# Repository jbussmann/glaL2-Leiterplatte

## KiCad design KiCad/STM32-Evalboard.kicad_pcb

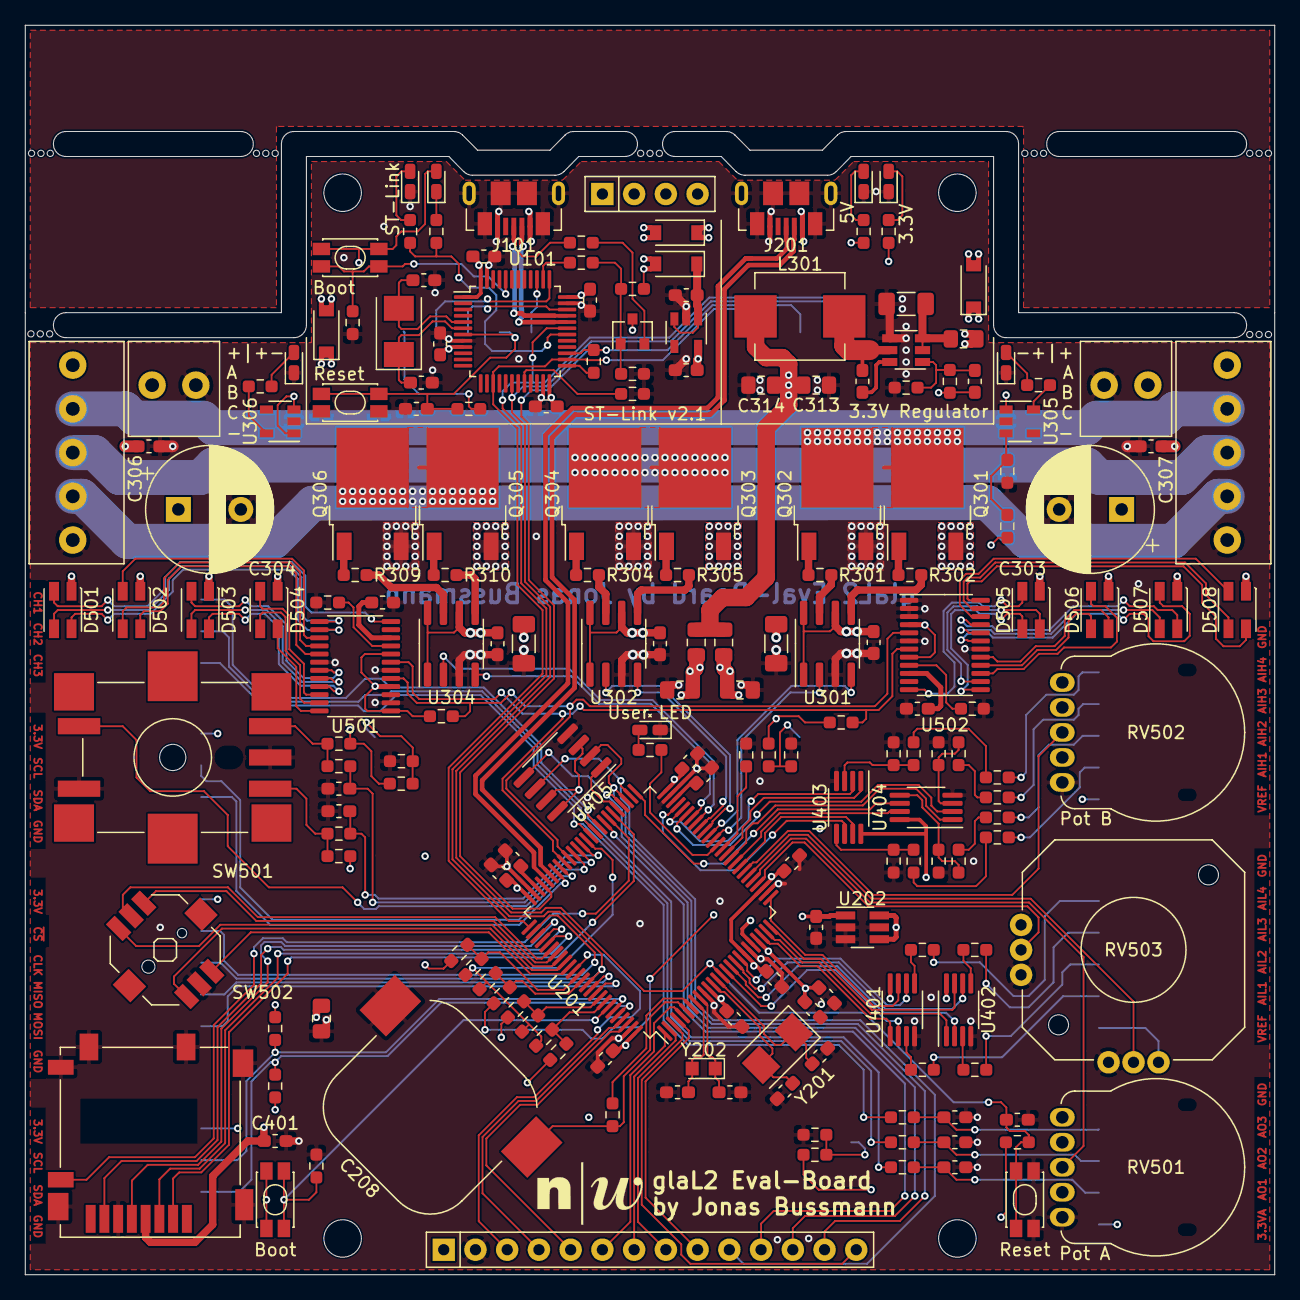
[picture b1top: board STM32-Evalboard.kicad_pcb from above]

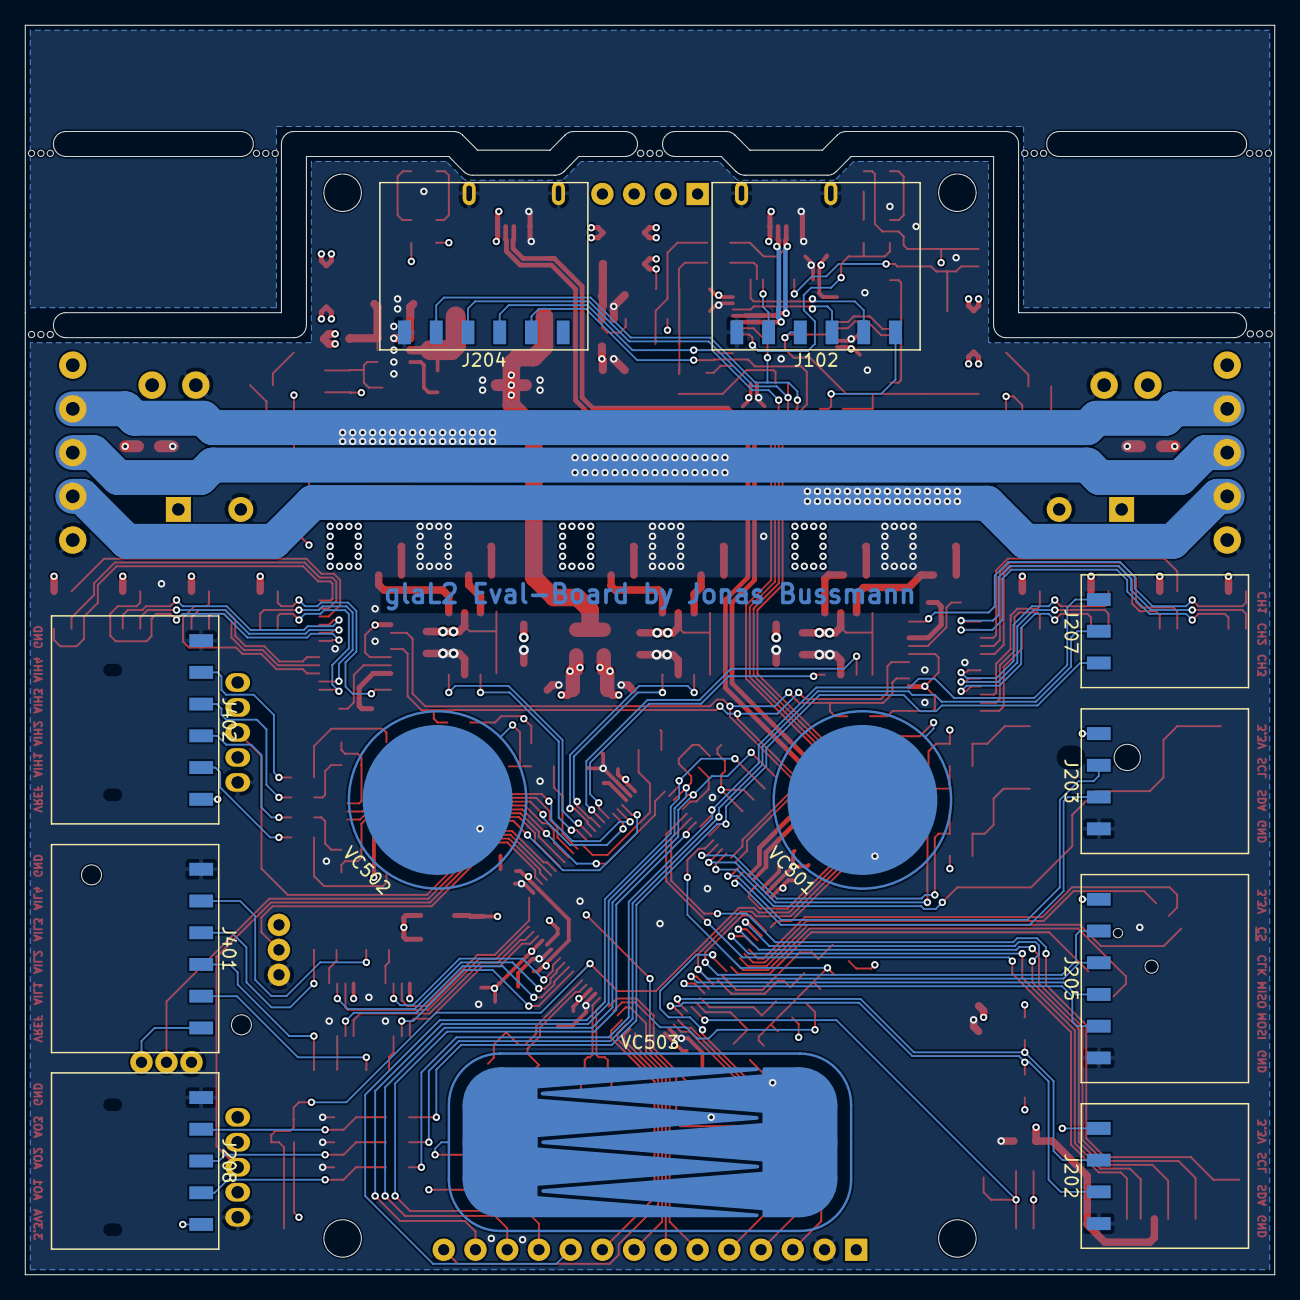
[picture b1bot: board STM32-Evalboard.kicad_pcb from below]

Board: 4 copper layers, 100.0 x 100.0 mm, 207 parts (12 on the bottom side), 200 nets.

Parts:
C101, C103, C105, C106, C107, C209, C210, C211, C213, C214, C216, C218, C220, C306, C307, C310, C401: 100n; C_0603_1608Metric_Pad1.05x0.95mm_HandSolder
C102, C104, C201, C203: 27p; C_0603_1608Metric_Pad1.05x0.95mm_HandSolder
C108, C109, C202, C204, C205, C212, C504: 1u; C_0603_1608Metric_Pad1.05x0.95mm_HandSolder
C206, C207: 1p; C_0603_1608Metric_Pad1.05x0.95mm_HandSolder
C208: 4F; SuperCap_196_HVC
C215, C217: 2u2; C_0603_1608Metric_Pad1.05x0.95mm_HandSolder
C219: 300p; C_0603_1608Metric_Pad1.05x0.95mm_HandSolder
C221: 4u7; C_0805_2012Metric_Pad1.15x1.40mm_HandSolder
C301, C302: 10u; C_1206_3216Metric_Pad1.33x1.80mm_HandSolder
C303, C304: 220u; CP_Radial_D10.0mm_P5.00mm
C305, C308, C312: 220n; C_0603_1608Metric_Pad1.05x0.95mm_HandSolder
C309: 22u; C_1206_3216Metric_Pad1.33x1.80mm_HandSolder
C311: 47p; C_0603_1608Metric_Pad1.05x0.95mm_HandSolder
C313, C314, C315, C316: 47u; C_0805_2012Metric_Pad1.15x1.40mm_HandSolder
C501, C502: 10n; C_0603_1608Metric_Pad1.05x0.95mm_HandSolder
C503: 1uF; C_0603_1608Metric_Pad1.05x0.95mm_HandSolder
D101, D102, D103, D302: PMEG3020; D_SOD-123
D104, D105: ST-Link; LED_0603_1608Metric_Castellated
D201: User LED; LED_0603_1608Metric_Castellated
D301: VBUS; LED_0603_1608Metric_Castellated
D303: 3V3; LED_0603_1608Metric_Castellated
D304: 11V; R_0603_1608Metric_Pad0.98x0.95mm_HandSolder
D305: >12V; LED_0603_1608Metric_Castellated
D306: <12V; LED_0603_1608Metric_Castellated
D501, D502, D503, D504, D505, D506, D507, D508: LED_ARGB; LED_PLCC4_3.2x2.8mm
FB301, FB302, FB303: 600R; R_0805_2012Metric_Pad1.15x1.40mm_HandSolder
H101, H102, H103, H104: MountingHole; MountingHole_3mm
J101: USB_ST-LINK; MicroUSB_GCT
J102: SWD_ST-LINK; PinSocket_Samtec_SMH_1x06_P2.54mm
J103: LCD_Support; PinSocket_1x04_P2.54mm_Display
J201: USB_MCU; MicroUSB_GCT
J202: I2C1; PinSocket_Samtec_SMH_1x04_P2.54mm
J203: USART1; PinSocket_Samtec_SMH_1x04_P2.54mm
J204: SWD_MCU; PinSocket_Samtec_SMH_1x06_P2.54mm
J205: SPI1; PinSocket_Samtec_SMH_1x06_P2.54mm
J206: LCD_1; PinSocket_1x14_P2.54mm_Display
J207: TIM4; PinSocket_Samtec_SMH_1x03_P2.54mm
J208: AOUT; PinSocket_Samtec_SMH_1x05_P2.54mm
J301: Power_left; TerminalBlock_Amphenol_1x02_P3.50mm
J302: Power_right; TerminalBlock_Amphenol_1x02_P3.50mm
J303: Terminal_left; TerminalBlock_Amphenol_1x05_P3.50mm
J304: Terminal_right; TerminalBlock_Amphenol_1x05_P3.50mm
J401: AIN_Low_Volt; PinSocket_Samtec_SMH_1x06_P2.54mm
J402: AIN_High_Volt; PinSocket_Samtec_SMH_1x06_P2.54mm
J403: Micro-SD; MicroSD_Molex
L301: 5.6u; Inductor_7.2x6.65x3.0mm
Q101: Q_NPN_BCE; SOT-23
Q301, Q303, Q305: STD36P4LLF6; TO-252-2
Q302, Q304, Q306: STD64N4F6; TO-252-2
R101, R102, R105, R107, R210, R211, R212, R401, R402, R403, R404, R405, R406, R407, R408, R501, R502, R504, R505, R506, R507, R508, R509, R511, R512, R514, R515, R516, R518: 10k; R_0603_1608Metric_Pad0.98x0.95mm_HandSolder
R103, R104, R201, R202, R203: 100R; R_0603_1608Metric_Pad0.98x0.95mm_HandSolder
R106: 36k; R_0603_1608Metric_Pad0.98x0.95mm_HandSolder
R108, R303: 1k5; R_0603_1608Metric_Pad0.98x0.95mm_HandSolder
R109, R110, R308, R312, R313: 680R; R_0603_1608Metric_Pad0.98x0.95mm_HandSolder
R204, R209: 220R; R_0603_1608Metric_Pad0.98x0.95mm_HandSolder
R205, R206, R207, R208, R519, R520: 4k7; R_0603_1608Metric_Pad0.98x0.95mm_HandSolder
R301, R302, R304, R305, R309, R310: 0R; R_0603_1608Metric_Pad0.98x0.95mm_HandSolder
R306: 47k; R_0603_1608Metric_Pad0.98x0.95mm_HandSolder
R307: 15k; R_0603_1608Metric_Pad0.98x0.95mm_HandSolder
R311: 1k; R_0603_1608Metric_Pad0.98x0.95mm_HandSolder
R409, R411, R413, R415: 120k; R_0603_1608Metric_Pad0.98x0.95mm_HandSolder
R410, R412, R414, R416: 2k2; R_0603_1608Metric_Pad0.98x0.95mm_HandSolder
R503, R510, R513, R517: 1M; R_0603_1608Metric_Pad0.98x0.95mm_HandSolder
RV501, RV502: RKJ1; Potentiometer_Alps
RV503: Adafruit; Thumbstick_Adafruit
SW101, SW202: Boot; Button_KMR4
SW102, SW201: Reset; Button_KMR4
SW501: PEC11S; RotaryEncoder_Bourns
SW502: SKRH; MultiSwitch_Alps
U101: STM32F103CBTx; LQFP-48_7x7mm_P0.5mm
U102: MIC5504-3.3YM5; SOT-23-5
U201: STM32F411VCTx; LQFP-100_14x14mm_P0.5mm
U202: MCP1501; SOT-23-6_Handsoldering
U301, U302, U304: FAN3278; SOIC-8_3.9x4.9mm_P1.27mm
U303: AP63300; TSOT-23-6
U305, U306: AP7380-33W5; SOT-23-5
U401, U402, U403, U404: MCP6G02; MSOP-8_3x3mm_P0.65mm
U405: AT25SF321B-SHB; SOIC-8_3.9x4.9mm_P1.27mm
U501, U502: LP5012; TSSOP-24_4.4x7.8mm_P0.65mm
VC501, VC502: Touch_Button
VC503: Touch_Slider
Y101, Y201: F90800021; Crystal_SMD_5032-2Pin_5.0x3.2mm
Y202: CM8V-T1A; Crystal_SMD_2012-2Pin_2.0x1.2mm_HandSoldering

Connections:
+3.3VA: C210.1, C212.1, C316.2, FB303.1, J208.5, U201.22, U202.4, U202.6
+3V0: C219.1, J401.6, J402.6, RV501.1, RV502.1, RV503.1b, RV503.3a, U201.21, U202.1, U401.8, U402.8, U403.8, U404.8
+3V3: C209.1, C211.1, C214.1, C216.1, C218.1, C220.1, C221.1, C315.2, C401.1, D501.1, D502.1, D503.1, D504.1, D505.1, D506.1, D507.1, D508.1, FB302.1, J202.4, J203.4, J205.6, J206.1, J403.4, R205.1, R206.1, R207.1, R208.1, R210.1, R501.2, R505.1, R507.1, R509.2, R515.2, SW202.1, U201.11, U201.19, U201.28, U201.50, U201.75, U201.100, U405.3, U405.7, U405.8, U501.1, U501.4, U501.8, U502.4, U502.8
+VDC: C301.1, C302.1, C303.1, C304.1, C305.1, C306.1, C307.1, C308.1, C312.1, D102.1, D302.1, D304.1, FB301.2, J301.1, J302.2, J303.5, J304.1, Q301.3, Q303.3, Q305.3, U301.1, U301.6, U301.8, U302.1, U302.6, U302.8, U304.1, U304.6, U304.8, U305.1, U306.1, U306.3
/BOOT0: R101.1, SW101.1, U101.44
/BOOT1: R102.1, U101.20
/HSE_IN: C104.1, U101.5, Y101.2
/HSE_OUT: C102.1, U101.6, Y101.1
/Interface/2AX_H: RV503.2b, U201.31
/Interface/2AX_V: RV503.2a, U201.29
/Interface/ENC_A: C501.1, R502.2, U201.63
/Interface/ENC_B: C502.1, R508.1, U201.64
/Interface/ENC_SW: SW501.S2, U201.65
/Interface/POT_A: RV501.2, U201.30
/Interface/POT_B: RV502.2, U201.32
/Interface/RGB_SCL: R206.2, U201.67, U501.7, U502.7
/Interface/RGB_SDA: R208.2, U201.66, U501.5, U502.5
/Interface/SW_Center: SW502.2, U201.81
/Interface/SW_Down: SW502.6, U201.84
/Interface/SW_Left: SW502.3, U201.83
/Interface/SW_Right: SW502.4, U201.85
/Interface/SW_Up: SW502.1, U201.82
/Interface/T_BUTTON1: R503.2, R504.1, U201.87
/Interface/T_BUTTON2: R510.2, R511.1, U201.88
/Interface/T_LOAD: R503.1, R510.1, R513.1, R517.1, U201.62
/Interface/T_SLIDER1: R513.2, R514.1, U201.92
/Interface/T_SLIDER2: R517.2, R518.1, U201.93
/LED: R109.1, R110.1, U101.30
/Microcontroller/AIN_H1: U201.33, U403.7
/Microcontroller/AIN_H2: U201.34, U404.7
/Microcontroller/AIN_H3: U201.35, U404.1
/Microcontroller/AIN_H4: U201.36, U403.1
/Microcontroller/AIN_L1: U201.23, U401.1
/Microcontroller/AIN_L2: U201.24, U402.1
/Microcontroller/AIN_L3: U201.25, U402.7
/Microcontroller/AIN_L4: U201.26, U401.7
/Microcontroller/BOOT0: R211.1, SW202.2, U201.94
/Microcontroller/BOOT1: R212.1, U201.37
/Microcontroller/FLASH_CLK: J206.10, U201.52, U405.6
/Microcontroller/FLASH_MISO: J206.13, U201.53, U405.2
/Microcontroller/FLASH_MOSI: J206.12, U201.54, U405.5
/Microcontroller/FLASH_~CS: U201.55, U405.1
/Microcontroller/GSEL_H1: U201.47, U403.6
/Microcontroller/GSEL_H2: U201.51, U404.6
/Microcontroller/GSEL_H3: U201.45, U404.2
/Microcontroller/GSEL_H4: U201.46, U403.2
/Microcontroller/GSEL_L1: U201.15, U401.2
/Microcontroller/GSEL_L2: U201.16, U402.2
/Microcontroller/GSEL_L3: U201.17, U402.6
/Microcontroller/GSEL_L4: U201.18, U401.6
/Microcontroller/HSE_IN: C203.1, U201.12, Y201.2
/Microcontroller/HSE_OUT: C201.1, U201.13, Y201.1
/Microcontroller/I2C1_SCL: J202.3, R205.2, U201.95
/Microcontroller/I2C1_SDA: J202.2, R207.2, U201.96
/Microcontroller/LCD_CLK: J206.7, U201.1
/Microcontroller/LCD_D~C: J206.5, U201.98
/Microcontroller/LCD_LED: J206.8, U201.2
/Microcontroller/LCD_MISO: J206.9, U201.4
/Microcontroller/LCD_MOSI: J206.6, U201.5
/Microcontroller/LCD_~CS: J206.3, U201.86
/Microcontroller/LCD_~RES: J206.4, U201.97
/Microcontroller/LED: R204.1, U201.38
/Microcontroller/LSE_IN: C207.1, U201.8, Y202.2
/Microcontroller/LSE_OUT: C206.1, U201.9, Y202.1
/Microcontroller/PHA_H: U201.40, U301.4
/Microcontroller/PHA_L: U201.39, U301.2
/Microcontroller/PHB_H: U201.42, U302.4
/Microcontroller/PHB_L: U201.41, U302.2
/Microcontroller/PHC_H: U201.44, U304.4
/Microcontroller/PHC_L: U201.43, U304.2
/Microcontroller/SD_CLK: J403.5, U201.78
/Microcontroller/SD_DET: J403.9, U201.57
/Microcontroller/SD_MISO: J403.7, U201.79
/Microcontroller/SD_MOSI: J403.3, U201.80
/Microcontroller/SD_~CS: J403.2, U201.56
/Microcontroller/SPI1_MISO: J205.3, U201.90
/Microcontroller/SPI1_MOSI: J205.2, U201.91
/Microcontroller/SPI1_~CS: J205.5, U201.77
/Microcontroller/TIM4_CH1: J207.3, R201.2, U201.59
/Microcontroller/TIM4_CH2: J207.2, R202.2, U201.60
/Microcontroller/TIM4_CH3: J207.1, R203.2, U201.61
/Microcontroller/TOUCH_IRQ: J206.14, U201.3
/Microcontroller/TOUCH_~CS: J206.11, U201.58
/Microcontroller/USART1_RX: J203.2, U201.69
/Microcontroller/USART1_TX: J203.3, U201.68
/Microcontroller/USB_D+: J201.3, U201.71
/Microcontroller/USB_D-: J201.2, U201.70
/Microcontroller/VBAT: C208.1, R209.2, U201.6
/Microcontroller/VBAT_Charge: R209.1, U201.7
/Microcontroller/VCAP1: C215.1, U201.48
/Microcontroller/VCAP2: C217.1, U201.73
/Power/Phase_A: J303.4, J304.2, Q301.2, Q302.2
/Power/Phase_B: J303.3, J304.3, Q303.2, Q304.2
/Power/Phase_C: J303.2, J304.4, Q305.2, Q306.2
/STL_SWCLK: J204.2, U101.15, U101.26, U201.76
/STL_SWDIO: J204.3, R104.2, U101.27, U201.72
/STL_SWO: J204.5, J205.4, U101.31, U201.89
/STL_~RST: C213.1, J204.4, R210.2, SW201.1, U101.18, U201.14
/SWDIO_IN: R104.1, U101.25
/SWD_3V3: C101.1, C103.1, C105.1, C106.1, C109.1, D104.2, J102.1, Q101.3, R107.1, SW101.2, U101.1, U101.9, U101.24, U101.36, U101.48, U102.5
/SWD_CLK: J102.2, U101.37
/SWD_DIO: J102.3, U101.34
/SWD_O: J102.5, U101.39
/SWD_~RST: C107.1, J102.4, R107.2, SW102.1, U101.7
/USB_5V: D101.2, D102.2, D103.2, J101.1, R105.1
/USB_D+: J101.3, R108.2, U101.33
/USB_D-: J101.2, U101.32
/USB_~RENUM: R103.2, U101.38
GND: C101.2, C102.2, C103.2, C104.2, C105.2, C106.2, C107.2, C108.2, C109.2, C201.2, C202.1, C203.2, C204.1, C205.1, C206.2, C207.2, C208.2, C209.2, C210.2, C211.2, C212.2, C213.2, C214.2, C215.2, C216.2, C217.2, C218.2, C219.2, C220.2, C221.2, C301.2, C302.2, C303.2, C304.2, C305.2, C306.2, C307.2, C308.2, C309.2, C312.2, C313.2, C314.2, C315.1, C316.1, C401.2, C501.2, C502.2, C503.2, C504.2, D105.1, D201.1, D301.1, D303.1, D305.1, D306.1, J101.5, J101.6, J102.6, J201.5, J201.6, J202.1, J203.1, J204.6, J205.1, J206.2, J208.1, J301.2, J302.1, J303.1, J304.5, J401.1, J402.1, J403.6, J403.10, J403.11, Q302.3, Q304.3, Q306.3, R101.2, R102.2, R106.2, R211.2, R212.2, R307.2, R311.2, R410.2, R412.2, R414.2, R416.2, R506.1, R512.1, R516.1, R519.2, R520.2, RV501.3, RV502.3, RV503.1a, RV503.3b, SW102.2, SW201.2, SW501.C, SW501.S1, SW502.5, U101.8, U101.23, U101.35, U101.47, U102.2, U201.10, U201.20, U201.27, U201.49, U201.74, U201.99, U202.2, U202.3, U202.5, U301.3, U302.3, U303.4, U304.3, U305.2, U306.2, U401.4, U402.4, U403.4, U404.4, U405.4, U501.2, U501.3, U501.6, U501.18, U502.1, U502.2, U502.3, U502.6, U502.18
unnamed: C108.1, D103.1, U102.1, U102.3
unnamed: C202.2, J208.4, R201.1
unnamed: C204.2, J208.3, R202.1
unnamed: C205.2, J208.2, R203.1
unnamed: C309.1, FB301.1, U303.2, U303.3
unnamed: C310.1, L301.1, U303.5
unnamed: C310.2, U303.6
unnamed: C311.1, C313.1, C314.1, FB302.2, FB303.2, L301.2, R306.1, R308.1
unnamed: C311.2, R306.2, R307.1, U303.1
unnamed: C503.1, U501.10
unnamed: C504.1, U502.10
unnamed: D104.1, R109.2
unnamed: D105.2, R110.2
unnamed: D201.2, R204.2
unnamed: D301.2, R303.2
unnamed: D303.2, R308.2
unnamed: D304.2, R311.1, U305.3
unnamed: D305.2, R312.2
unnamed: D306.2, R313.2
unnamed: D501.2, U501.12
unnamed: D501.3, U501.13
unnamed: D501.4, U501.14
unnamed: D502.2, U501.15
unnamed: D502.3, U501.16
unnamed: D502.4, U501.17
unnamed: D503.2, U501.19
unnamed: D503.3, U501.20
unnamed: D503.4, U501.21
unnamed: D504.2, U501.22
unnamed: D504.3, U501.23
unnamed: D504.4, U501.24
unnamed: D505.2, U502.12
unnamed: D505.3, U502.13
unnamed: D505.4, U502.14
unnamed: D506.2, U502.15
unnamed: D506.3, U502.16
unnamed: D506.4, U502.17
unnamed: D507.2, U502.19
unnamed: D507.3, U502.20
unnamed: D507.4, U502.21
unnamed: D508.2, U502.22
unnamed: D508.3, U502.23
unnamed: D508.4, U502.24
unnamed: J401.2, R404.2
unnamed: J401.3, R403.2
unnamed: J401.4, R402.2
unnamed: J401.5, R401.2
unnamed: J402.2, R408.2
unnamed: J402.3, R407.2
unnamed: J402.4, R406.2
unnamed: J402.5, R405.2
unnamed: Q101.1, R103.1, R105.2, R106.1
unnamed: Q101.2, R108.1
unnamed: Q301.1, R302.1
unnamed: Q302.1, R301.1
unnamed: Q303.1, R305.1
unnamed: Q304.1, R304.1
unnamed: Q305.1, R310.1
unnamed: Q306.1, R309.1
unnamed: R301.2, U301.7
unnamed: R302.2, U301.5
unnamed: R304.2, U302.7
unnamed: R305.2, U302.5
unnamed: R309.2, U304.7
unnamed: R310.2, U304.5
unnamed: R312.1, U305.5
unnamed: R313.1, U306.5
unnamed: R401.1, U401.3
unnamed: R402.1, U402.3
unnamed: R403.1, U402.5
unnamed: R404.1, U401.5
unnamed: R405.1, R409.1
unnamed: R406.1, R411.1
unnamed: R407.1, R413.1
unnamed: R408.1, R415.1
unnamed: R409.2, R410.1, U403.5
unnamed: R411.2, R412.1, U404.5
unnamed: R413.2, R414.1, U404.3
unnamed: R415.2, R416.1, U403.3
unnamed: R501.1, R506.2, VC501.2
unnamed: R502.1, R505.2, SW501.A
unnamed: R504.2, VC501.1
unnamed: R507.2, R508.2, SW501.B
unnamed: R509.1, R512.2, VC502.2
unnamed: R511.2, VC502.1
unnamed: R514.2, VC503.1
unnamed: R515.1, R516.2, VC503.3
unnamed: R518.2, VC503.2
unnamed: R519.1, U501.9
unnamed: R520.1, U502.9
VBUS: D101.1, D302.2, J201.1, R303.1

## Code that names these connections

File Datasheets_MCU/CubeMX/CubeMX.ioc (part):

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Mcu.Name=STM32F411V(C-E)Tx
Mcu.Package=LQFP100
Mcu.UserName=STM32F411VCTx
PA0-WKUP.Signal=ADCx_IN0
PA1.Signal=ADCx_IN1
PA10.Mode=Asynchronous
PA10.Signal=USART1_RX
PA11.Mode=Host_Only
PA11.Signal=USB_OTG_FS_DM
PA12.Mode=Host_Only
PA12.Signal=USB_OTG_FS_DP
PA13.Mode=Serial_Wire
PA13.Signal=SYS_JTMS-SWDIO
PA14.Mode=Serial_Wire
PA14.Signal=SYS_JTCK-SWCLK
PA15.Mode=NSS_Signal_Hard_Input
PA15.Signal=SPI1_NSS
PA2.Signal=ADCx_IN2
PA3.Signal=ADCx_IN3
PA4.Signal=ADCx_IN4
PA5.Signal=ADCx_IN5
PA6.Signal=ADCx_IN6
PA7.Signal=ADCx_IN7
PA8.GPIOParameters=GPIO_Label
PA8.GPIO_Label=LED_SCL
PA8.Mode=I2C
PA8.Signal=I2C3_SCL
PA9.Mode=Asynchronous
PA9.Signal=USART1_TX
PB0.Signal=ADCx_IN8
PB1.Signal=ADCx_IN9
PB10.GPIOParameters=GPIO_Label
PB10.GPIO_Label=GSEL_H1
PB10.Signal=GPIO_Output
PB12.GPIOParameters=GPIO_Label
PB12.GPIO_Label=GSEL_H2
PB12.Signal=GPIO_Output
PB13.GPIOParameters=GPIO_Label
PB13.GPIO_Label=TOUCH/FLASH_SCK
PB13.Mode=Full_Duplex_Master
PB13.Signal=SPI2_SCK
PB14.GPIOParameters=GPIO_Label
PB14.GPIO_Label=TOUCH/FLASH_MISO
PB14.Mode=Full_Duplex_Master
PB14.Signal=SPI2_MISO
PB15.GPIOParameters=GPIO_Label
PB15.GPIO_Label=TOUCH/FLASH_MOSI
PB15.Mode=Full_Duplex_Master
PB15.Signal=SPI2_MOSI
PB2.GPIOParameters=GPIO_Label
PB2.GPIO_Label=BOOT1
PB2.Signal=GPIO_Input
PB3.Mode=Full_Duplex_Master
PB3.Signal=SPI1_SCK
PB4.Mode=Full_Duplex_Master
PB4.Signal=SPI1_MISO
PB5.Mode=Full_Duplex_Master
PB5.Signal=SPI1_MOSI
PB6.GPIOParameters=GPIO_Label
PB6.GPIO_Label=T_SLIDER1
PB6.Signal=GPIO_Output
PB7.GPIOParameters=GPIO_Label
PB7.GPIO_Label=T_SLIDER2
PB7.Signal=GPIO_Output
PB8.Mode=I2C
PB8.Signal=I2C1_SCL
PB9.Mode=I2C
PB9.Signal=I2C1_SDA
PC0.GPIOParameters=GPIO_Label
PC0.GPIO_Label=GSEL_L1
PC0.Signal=GPIO_Output
PC1.GPIOParameters=GPIO_Label
PC1.GPIO_Label=GSEL_L2
PC1.Signal=GPIO_Output
PC10.GPIOParameters=GPIO_Label
PC10.GPIO_Label=SD_SCK
PC10.Mode=Full_Duplex_Master
PC10.Signal=SPI3_SCK
PC11.GPIOParameters=GPIO_Label
PC11.GPIO_Label=SD_MISO
PC11.Mode=Full_Duplex_Master
PC11.Signal=SPI3_MISO
PC12.GPIOParameters=GPIO_Label
PC12.GPIO_Label=SD_MOSI
PC12.Mode=Full_Duplex_Master
PC12.Signal=SPI3_MOSI
PC13-ANTI_TAMP.GPIOParameters=GPIO_Label
PC13-ANTI_TAMP.GPIO_Label=Vbat_Charge
PC13-ANTI_TAMP.Signal=GPIO_Output
PC14-OSC32_IN.Mode=LSE-External-Oscillator
PC14-OSC32_IN.Signal=RCC_OSC32_IN
PC15-OSC32_OUT.Mode=LSE-External-Oscillator
PC15-OSC32_OUT.Signal=RCC_OSC32_OUT
PC2.GPIOParameters=GPIO_Label
PC2.GPIO_Label=GSEL_L3
PC2.Signal=GPIO_Output
PC3.GPIOParameters=GPIO_Label
PC3.GPIO_Label=GSEL_L4
PC3.Signal=GPIO_Output
PC4.Signal=ADCx_IN14
PC5.Signal=ADCx_IN15
PC6.GPIOParameters=GPIO_Label
PC6.GPIO_Label=ENC_A
PC6.Signal=S_TIM3_CH1
PC7.GPIOParameters=GPIO_Label
PC7.GPIO_Label=ENC_B
PC7.Signal=S_TIM3_CH2
PC8.GPIOParameters=GPIO_Label
PC8.GPIO_Label=ENC_SW
PC8.Signal=GPIO_Input
PC9.GPIOParameters=GPIO_Label
PC9.GPIO_Label=LED_SDA
PC9.Mode=I2C
PC9.Signal=I2C3_SDA
PD0.GPIOParameters=GPIO_Label
PD0.GPIO_Label=SW_L
PD0.Signal=GPIO_Input
PD1.GPIOParameters=GPIO_Label
PD1.GPIO_Label=SW_C
PD1.Signal=GPIO_Input
PD10.GPIOParameters=GPIO_Label
PD10.GPIO_Label=SD_DET
PD10.Signal=GPIO_Input
PD11.GPIOParameters=GPIO_Label
PD11.GPIO_Label=TOUCH_CS
PD11.Signal=GPIO_Output
PD12.Signal=S_TIM4_CH1
PD13.Signal=S_TIM4_CH2
PD14.Signal=S_TIM4_CH3
PD15.GPIOParameters=GPIO_Label
PD15.GPIO_Label=T_LOAD
PD15.Signal=GPIO_Output
PD2.GPIOParameters=GPIO_Label
PD2.GPIO_Label=SW_R
PD2.Signal=GPIO_Input
PD3.GPIOParameters=GPIO_Label
PD3.GPIO_Label=SW_D
PD3.Signal=GPIO_Input
PD4.GPIOParameters=GPIO_Label
PD4.GPIO_Label=SW_U
PD4.Signal=GPIO_Input
PD5.GPIOParameters=GPIO_Label
PD5.GPIO_Label=LCD_CS
PD5.Signal=GPIO_Output
PD6.GPIOParameters=GPIO_Label
PD6.GPIO_Label=T_BUTTON1
PD6.Signal=GPIO_Output
PD7.GPIOParameters=GPIO_Label
PD7.GPIO_Label=T_BUTTON2
PD7.Signal=GPIO_Output
PD8.GPIOParameters=GPIO_Label
PD8.GPIO_Label=FLASH_~CS
PD8.Signal=GPIO_Output
PD9.GPIOParameters=GPIO_Label
PD9.GPIO_Label=SD_~CS
PD9.Signal=GPIO_Output
PE0.GPIOParameters=GPIO_Label
PE0.GPIO_Label=LCD_RESET
PE0.Signal=GPIO_Output
PE1.GPIOParameters=GPIO_Label
PE1.GPIO_Label=LCD_DC
PE1.Signal=GPIO_Output
PE10.Mode=PWM Generation2 CH2 CH2N
PE10.Signal=TIM1_CH2N
PE11.Signal=S_TIM1_CH2
PE12.Mode=PWM Generation3 CH3 CH3N
PE12.Signal=TIM1_CH3N
PE13.Signal=S_TIM1_CH3
PE14.GPIOParameters=GPIO_Label
PE14.GPIO_Label=GSEL_H3
PE14.Signal=GPIO_Output
PE15.GPIOParameters=GPIO_Label
PE15.GPIO_Label=GSEL_H4
PE15.Signal=GPIO_Output
PE2.GPIOParameters=GPIO_Label
PE2.GPIO_Label=LCD_SCK
PE2.Mode=Full_Duplex_Master
PE2.Signal=SPI5_SCK
PE3.GPIOParameters=GPIO_Label
PE3.GPIO_Label=LCD_LED
PE3.Signal=GPIO_Output
PE4.GPIOParameters=GPIO_Label
PE4.GPIO_Label=TOUCH_IRQ
PE4.Signal=GPIO_Output
PE5.GPIOParameters=GPIO_Label
PE5.GPIO_Label=LCD_MISO
PE5.Mode=Full_Duplex_Master
PE5.Signal=SPI5_MISO
PE6.GPIOParameters=GPIO_Label
PE6.GPIO_Label=LCD_MOSI
PE6.Mode=Full_Duplex_Master
PE6.Signal=SPI5_MOSI
PE7.GPIOParameters=GPIO_Label
PE7.GPIO_Label=LED
PE7.Signal=GPIO_Output
PE8.Mode=PWM Generation1 CH1 CH1N
PE8.Signal=TIM1_CH1N
PE9.Signal=S_TIM1_CH1
PH0\ -\ OSC_IN.Mode=HSE-External-Oscillator
PH0\ -\ OSC_IN.Signal=RCC_OSC_IN
PH1\ -\ OSC_OUT.Mode=HSE-External-Oscillator
PH1\ -\ OSC_OUT.Signal=RCC_OSC_OUT
RCC.HSE_VALUE=25000000
RCC.SYSCLKFreq_VALUE=16000000
board=custom

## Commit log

2021-03-08 project init
2021-03-08 add readme try to change account
2021-03-08 test
2021-08-02 project complete
